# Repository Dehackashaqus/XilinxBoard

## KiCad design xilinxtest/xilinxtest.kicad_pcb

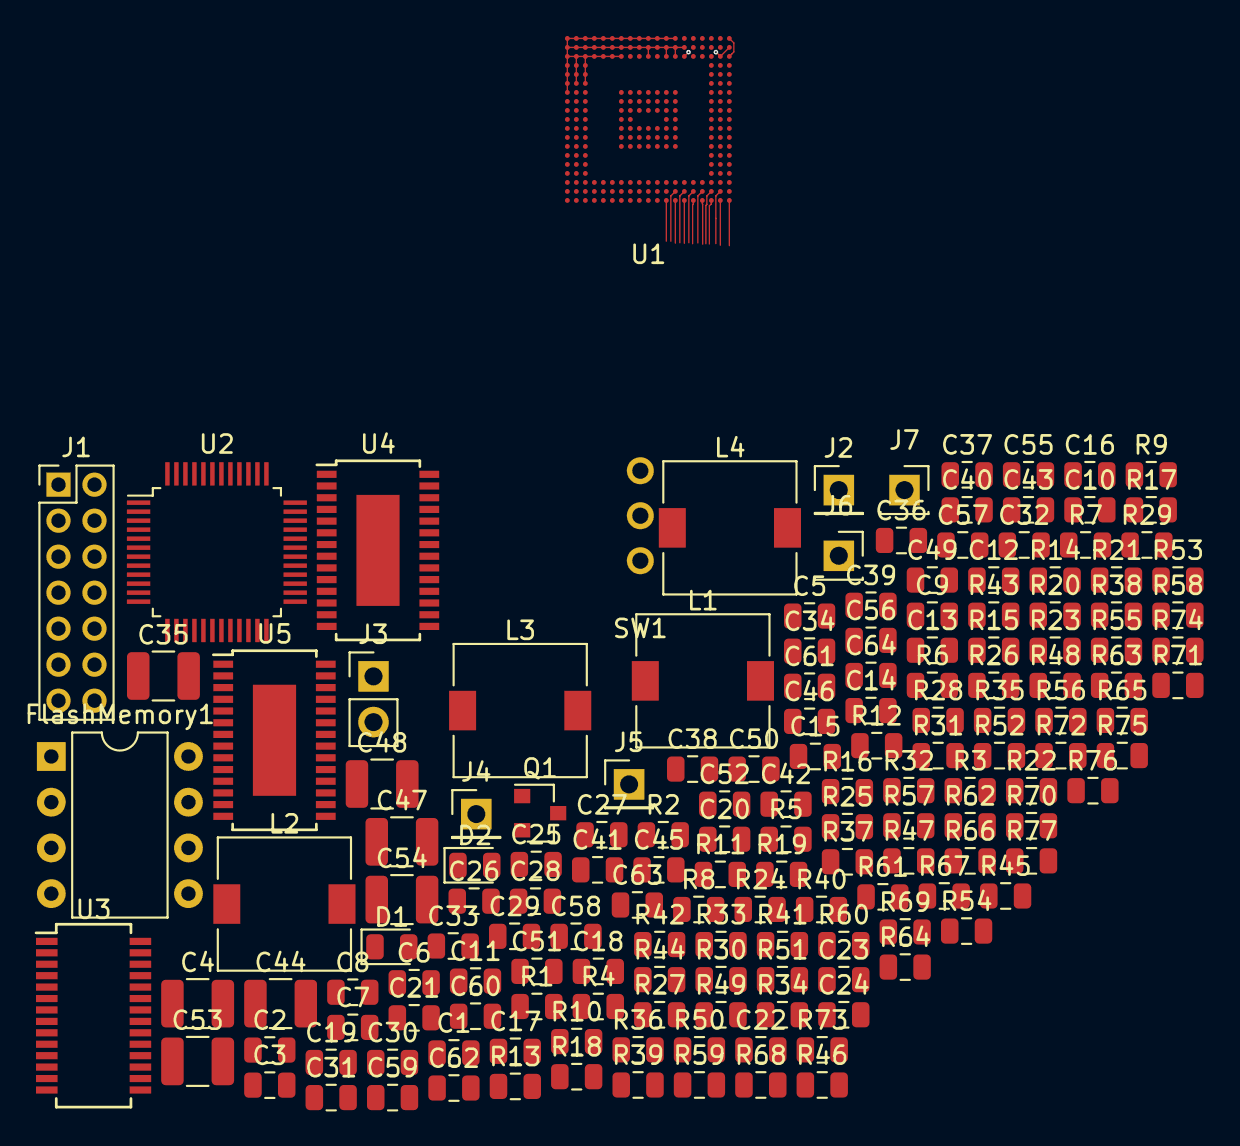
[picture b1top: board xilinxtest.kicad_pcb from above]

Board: 4 copper layers, 162 parts (0 on the bottom side), 146 nets.

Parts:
C1, C7, C8, C20, C24, C27, C28, C30, C36, C57: 47nF; C_0805_2012Metric
C2, C11, C13, C18, C26, C29, C32, C40, C60: 470nF; C_0805_2012Metric
C3, C14, C15, C19, C33, C34, C41: 4.7uF; C_0805_2012Metric
C4, C35, C44, C47, C48, C53, C54: 100uF; C_1210_3225Metric
C5, C9, C12, C23: 0.1uF; C_0805_2012Metric
C6: 1uF; C_0805_2012Metric
C10: 10uF; C_0805_2012Metric
C16, C17, C22, C51, C52, C58, C59: 47uF; C_0805_2012Metric
C21, C37, C38, C39, C42, C43, C55, C56, C61, C62, C64: 100nF; C_0805_2012Metric
C25, C31, C45, C46, C49, C50: 2.2uF; C_0805_2012Metric
C63: 4.7nF; C_0805_2012Metric
D1: LED; D_0805_2012Metric
D2: LG R971; LED_0805_2012Metric
FlashMemory1: Conn_02x04_Counter_Clockwise; DIP-8_W7.62mm
J1: Conn_02x07_Odd_Even; PinHeader_2x07_P2.00mm_Vertical
J2: -INPUT; PinHeader_1x01_P2.54mm_Vertical
J3: GNDJUMP; PinHeader_1x02_P2.54mm_Vertical
J4: +INPUT; PinHeader_1x01_P2.54mm_Vertical
J5: OutputGND; PinHeader_1x01_P2.54mm_Vertical
J6: 5V_SUPPLY; PinSocket_1x01_P2.54mm_Vertical
J7: GND_SUPPLY; PinSocket_1x01_P2.54mm_Vertical
L1, L2, L3, L4: 1.5u; L_7.3x7.3_H4.5
Q1: FDV301N; SOT-23
R1, R2, R3, R4, R5, R6, R7, R8, R9, R10, R11, R18, R20, R21, R22, R23, R24, R25, R26, R27, R28, R29, R30, R31, R32, R33, R34, R35, R36, R37, R38, R39, R41, R42, R43, R44, R49, R50, R51, R52, R53, R54, R55, R56, R57, R58, R59, R60, R61, R62, R63, R64: 100; R_0805_2012Metric
R12, R15, R17, R40: 4.7K; R_0805_2012Metric
R13: 1k; R_0805_2012Metric
R14, R16: 1K; R_0805_2012Metric
R19: 200; R_0805_2012Metric
R45, R48: 100k; R_0805_2012Metric
R46, R47: 200k; R_0805_2012Metric
R65, R68: 13.3k; R_0805_2012Metric
R66, R67, R70, R71: 60.4k; R_0805_2012Metric
R69: 90.9k; R_0805_2012Metric
R72: 30.1k; R_0805_2012Metric
R73, R75, R77: 10k; R_0805_2012Metric
R74: 4.7k; R_0805_2012Metric
R76: 680; R_0805_2012Metric
SW1: SW_SPDT; SPDTSwitch
U1: XC7A35T-CPG236; CPG236
U2: ADS8412; LQFP-48_7x7mm_P0.5mm
U3: LTC1657; SSOP-28_3.9x9.9mm_P0.635mm
U4, U5: LTC3633-TSSOP; TSSOP-28-1EP_4.4x9.7mm_P0.65mm

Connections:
5V: C9.2, C10.2, C23.1, C45.1, C46.1, C49.1, C50.1, R45.2, R48.2, R74.1, U2.4, U2.9, U2.10, U2.13, U2.43, U2.46, U3.24, U4.9, U4.18, U4.24, U5.19, U5.24, U5.25
ADCBUSY: R6.2, U2.36
ADCCS: R5.2, U2.42
ADCRESET: R2.2, U2.38
AGND: C5.1, C6.1, C9.1, C10.1, U2.5, U2.8, U2.11, U2.12, U2.14, U2.15, U2.44, U2.45, U2.47, U2.48
ASYNCHDAC: R39.2, U1.W2
BDGND: C12.2, U2.25, U2.35
CONVSTART: R3.2, U2.40
D0: R37.2, U1.R18
D1: R36.2, U1.P18
D2: R35.2, U1.P17
D3: R34.2, U1.N17
D4: R33.2, U1.K17
D5: R32.2, U1.L17
D6: R31.2, U1.M19
D7: R30.2, U1.M18
D8: R29.2, U1.R19
D9: R28.2, U1.P19
D10: R27.2, U1.N19
D11: R26.2, U1.N18
D12: R25.2, U1.K18
D13: R24.2, U1.L18
D14: R23.2, U1.J18
D15: R22.2, U1.J17
DACCLR: R21.2, U1.V3
DACWRITE: R38.2, U1.V2
DAC_out: U3.25, U3.26
DB0: R49.2, U2.33
DB1: R50.2, U2.32
DB2: R51.2, U2.31
DB3: R52.2, U2.30
DB4: R53.2, U2.29
DB5: R54.2, U2.28
DB6: R55.2, U2.27
DB7: R56.2, U2.26
DB8: R57.2, U2.23
DB9: R58.2, U2.22
DB10: R59.2, U2.21
DB11: R60.2, U2.20
DB12: R61.2, U2.19
DB13: R62.2, U2.18
DB14: R63.2, U2.17
DB15: R64.2, U2.16
EN: C64.1, R77.1, U5.6
GND: C1.1, C2.1, C3.1, C4.1, C7.2, C8.1, C11.2, C13.1, C14.2, C15.1, C16.2, C17.2, C18.2, C19.2, C20.2, C21.2, C22.2, C23.2, C24.2, C25.2, C26.2, C27.2, C28.2, C29.2, C30.2, C31.2, C32.2, C33.2, C34.2, C35.2, C36.2, C37.2, C40.2, C41.2, C44.2, C45.2, C46.2, C47.1, C48.2, C49.2, C50.2, C51.1, C52.2, C53.1, C54.2, C55.1, C56.2, C57.2, C58.1, C59.2, C60.2, C61.1, C62.2, C63.2, C64.2, D1.1, FlashMemory1.4, J1.1, J1.3, J1.5, J1.7, J1.9, J1.11, J1.13, J3.2, J5.1, J7.1, Q1.2, R14.2, R16.2, R46.2, R47.2, R65.1, R68.2, R69.1, R72.2, R75.2, SW1.3, U1.A1, U1.A2, U1.A3, U1.A4, U1.A5, U1.A6, U1.A7, U1.A8, U1.A9, U1.A10, U1.A11, U1.A12, U1.A13, U1.A19, U1.B1, U1.B2, U1.B3, U1.B4, U1.B5, U1.B6, U1.B7, U1.B8, U1.B9, U1.B10, U1.B11, U1.B12, U1.B13, U1.B14, U1.C1, U1.C2, U1.C3, U1.C4, U1.C5, U1.C6, U1.C7, U1.C10, U1.C12, U1.C13, U1.C19, U1.D1, U1.D2, U1.D3, U1.E1, U1.E2, U1.E3, U1.E17, U1.F1, U1.F2, U1.F3, U1.F19, U1.G1, U1.G7, U1.G8, U1.G9, U1.G11, U1.H7, U1.H8, U1.H9, U1.H11, U1.H12, U1.H18, U1.J8, U1.J9, U1.J11, U1.J12, U1.K8, U1.L8, U1.L9, U1.L11, U1.L19, U1.M9, U1.M13, U1.N9, U1.N12, U1.N13, U1.P2, U1.T19, U1.U6, U1.U9, U1.V18, U1.W1, U1.W12, U2.39, U3.2, U3.3, U3.20, U3.21, U4.7, U4.10, U4.29, U5.10, U5.29
LEDPWRUP: Q1.1, R73.2, U4.4
unnamed: C5.2, C6.2, U2.1, U2.2
unnamed: C25.1, U4.1, U4.5, U4.14, U4.22
unnamed: C31.1, U5.1, U5.5, U5.7, U5.14, U5.21, U5.22
unnamed: C37.1, U4.21
unnamed: C38.1, L1.2, U4.26, U4.27
unnamed: C38.2, U4.23
unnamed: C39.1, U4.20
unnamed: C39.2, L2.2, U4.17
unnamed: C42.1, U5.20
unnamed: C42.2, L4.2, U5.16, U5.17
unnamed: C43.1, L3.2, U5.26, U5.27
unnamed: C43.2, U5.23
unnamed: D1.2, R20.2
unnamed: D2.1, Q1.3
unnamed: D2.2, R76.2
unnamed: FlashMemory1.1, R40.2, U1.K19
unnamed: FlashMemory1.2, R41.1
unnamed: FlashMemory1.3, R42.2
unnamed: FlashMemory1.5, R43.2
unnamed: FlashMemory1.6, R18.2, U1.C11
unnamed: FlashMemory1.7, R44.1
unnamed: J1.4, R9.1
unnamed: J1.6, R8.1
unnamed: J1.8, R7.2
unnamed: J1.10, R1.2
unnamed: J2.1, J3.1, R10.2
unnamed: J4.1, R11.1
unnamed: R1.1, U1.W10
unnamed: R2.1, U1.R2
unnamed: R3.1, U1.T2
unnamed: R4.1, U1.R3
unnamed: R5.1, U1.T3
unnamed: R6.1, U1.T1
unnamed: R7.1, U1.W8
unnamed: R8.2, R9.2, U1.C8, U1.W9
unnamed: R10.1, U2.7
unnamed: R11.2, U2.6
unnamed: R12.2, U1.V11
unnamed: R13.2, U1.V12
unnamed: R14.1, U1.U10
unnamed: R15.2, U1.V10
unnamed: R16.1, U1.W11
unnamed: R17.2, U1.U11
unnamed: R19.2, R20.1, U1.U12
unnamed: R21.1, U3.27
unnamed: R22.1, U3.19
unnamed: R23.1, U3.18
unnamed: R24.1, U3.17
unnamed: R25.1, U3.16
unnamed: R26.1, U3.15
unnamed: R27.1, U3.14
unnamed: R28.1, U3.13
unnamed: R29.1, U3.12
unnamed: R30.1, U3.11
unnamed: R31.1, U3.10
unnamed: R32.1, U3.9
unnamed: R33.1, U3.8
unnamed: R34.1, U3.7
unnamed: R35.1, U3.6
unnamed: R36.1, U3.5
unnamed: R37.1, U3.4
unnamed: R38.1, U3.1
unnamed: R39.1, U3.28
unnamed: R41.2, U1.D19
unnamed: R42.1, U1.G18
unnamed: R43.1, U1.D18
unnamed: R44.2, U1.F18
unnamed: R45.1, U4.6, U5.11
unnamed: R46.1, U4.8
unnamed: R47.1, U5.8
unnamed: R48.1, U5.4, U5.9
unnamed: R49.1, U1.W18
unnamed: R50.1, U1.W19
unnamed: R51.1, U1.T17
unnamed: R52.1, U1.T18
unnamed: R53.1, U1.U17
unnamed: R54.1, U1.U18
unnamed: R55.1, U1.V16
unnamed: R56.1, U1.V17
unnamed: R57.1, U1.W16
unnamed: R58.1, U1.W17
unnamed: R59.1, U1.V15
unnamed: R60.1, U1.W15
unnamed: R61.1, U1.W13
unnamed: R62.1, U1.W14
unnamed: R63.1, U1.U15
unnamed: R64.1, U1.U16
unnamed: R65.2, R66.1, U4.3
unnamed: R67.2, R68.1, U4.12
unnamed: R69.2, R70.1, U5.3
unnamed: R71.2, R72.1, U5.12
unnamed: R74.2, R75.1, SW1.2
unnamed: R77.2, SW1.1
unnamed: U3.22, U3.23
OUTENABLE: R4.2, U2.41
VCC1V0: C16.1, C19.1, C22.1, C24.1, C26.1, C27.1, C28.1, C29.1, C30.1, C32.1, C33.1, C34.1, C35.1, C53.2, C58.2, C61.2, L3.1, R70.2, U1.G10, U1.H10, U1.J10, U1.L10, U1.M10, U1.M11, U1.N10, U1.N11, U5.28
VCC1V8: C17.1, C18.1, C20.1, C54.1, C59.1, C62.1, L4.1, R71.1, U1.C9, U1.H13, U1.J13, U5.15
VCC3V3: C1.2, C2.2, C3.2, C4.2, C8.2, C13.2, C15.2, C36.1, C40.1, C41.1, C44.1, C57.1, C60.1, C63.1, U1.B19, U1.C14, U1.C18, U1.F17, U1.G13, U1.H3, U1.J7, U1.K1, U1.K7, U1.K12, U1.K13, U1.L7, U1.L12, U1.L13, U1.M7, U1.M8, U1.M12, U1.M17, U1.N7, U1.N8, U1.R1, U1.R17, U1.U13, U1.V1, U1.V6
VCC3V3ADCFLASH: C12.1, C48.1, C52.1, C56.1, FlashMemory1.8, L2.1, R40.1, R67.1, U2.24, U2.34, U2.37, U4.15
VCC3V3FPGA: C7.1, C11.1, C14.1, C21.1, C47.2, C51.2, C55.2, J1.2, L1.1, R12.1, R13.1, R15.1, R17.1, R18.1, R19.1, R66.2, R73.1, R76.1, U1.G12, U1.V9, U4.28

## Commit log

2018-12-03 Uploaded Communication Schematic
2018-12-04 Added some power components
2018-12-05 associated all footprints
2018-12-07 Started on PCB Layout
